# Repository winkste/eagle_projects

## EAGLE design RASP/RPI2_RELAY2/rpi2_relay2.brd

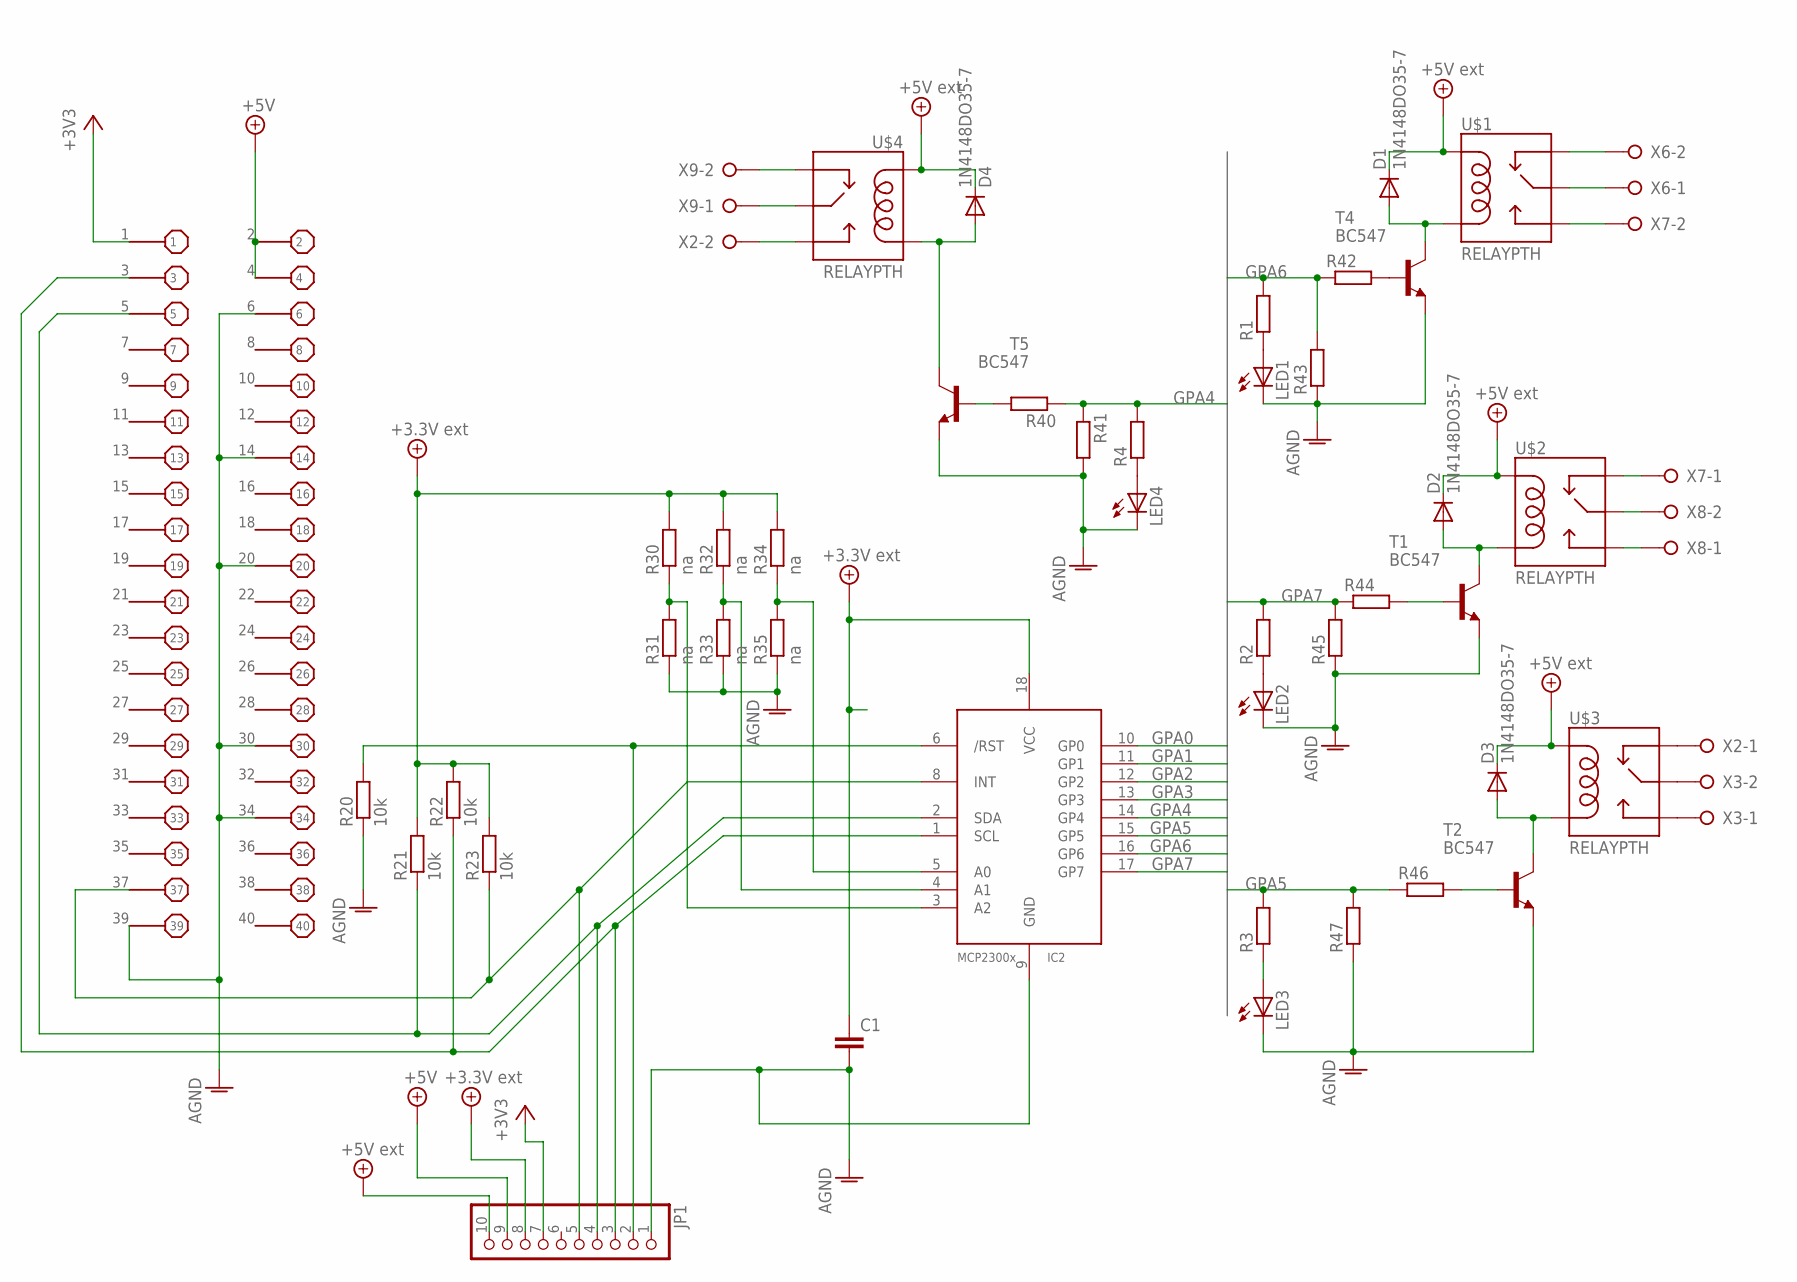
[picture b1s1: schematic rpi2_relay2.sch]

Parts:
C1: C-EUC1210; C1210
D1, D2, D3, D4: 1N4148DO35-7; DO35-7
IC2: MCP23008/P; DIL18
JP1: PINHD-1X10; 1X10
LED1, LED2, LED3, LED4: LEDCHIP-LED0805; CHIP-LED0805
R1, R2, R3, R4, R40, R41, R42, R43, R44, R45, R46, R47: R-EU_R0805; R0805
R20, R21, R22, R23: 10k; R0805
R30, R31, R32, R33, R34, R35: na; R0805
T1, T2, T4, T5: BC547; TO92
U$1, U$2, U$3, U$4: RELAYPTH; SRD-05VDC-SL-C
X1: B+_GPIO
X2, X3, X6, X7, X8, X9: W237-02P; W237-132

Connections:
3.3VEXT: C1.1, IC2.18 (VCC), JP1.8, R21.2, R22.2, R23.2, R30.2, R32.2, R34.2
+3V3: JP1.7, X1.1
+5V: JP1.9, X1.2, X1.4
+5V/1: D1.C, D2.C, D3.C, D4.C, JP1.10, U$1.COIL1, U$2.COIL1, U$3.COIL1, U$4.COIL1
AGND: C1.2, IC2.9 (GND), JP1.1, LED1.C, LED2.C, LED3.C, LED4.C, R20.1, R31.1, R33.1, R35.1, R41.2, R43.1, R45.1, R47.1, T1.1 (E), T2.1 (E), T4.1 (E), T5.1 (E), X1.6, X1.14, X1.20, X1.30, X1.34, X1.39
GPA0: IC2.10 (GP0)
GPA1: IC2.11 (GP1)
GPA2: IC2.12 (GP2)
GPA3: IC2.13 (GP3)
GPA4: IC2.14 (GP4), R4.2, R40.1, R41.1
GPA5: IC2.15 (GP5), R3.2, R46.1, R47.2
GPA6: IC2.16 (GP6), R1.2, R42.1, R43.2
GPA7: IC2.17 (GP7), R2.2, R44.1, R45.2
unnamed: R46.2, T2.2 (B)
unnamed: D1.A, T4.3 (C), U$1.COIL0
unnamed: IC2.1 (SCL), JP1.3, R22.1, X1.3
unnamed: IC2.2 (SDA), JP1.4, R21.1, X1.5
unnamed: LED1.A, R1.1
unnamed: IC2.8 (INT), JP1.5, R23.1, X1.37
unnamed: IC2.6 (/RST), JP1.2, R20.2
unnamed: R44.2, T1.2 (B)
unnamed: U$1.SWCOMMON, X6.1
unnamed: U$1.SWCLOSED (SWCLOSE), X6.2
unnamed: U$1.SWOPEN, X7.2
unnamed: D2.A, T1.3 (C), U$2.COIL0
unnamed: LED2.A, R2.1
unnamed: U$2.SWCLOSED (SWCLOSE), X7.1
unnamed: U$2.SWOPEN, X8.1
unnamed: U$2.SWCOMMON, X8.2
unnamed: D3.A, T2.3 (C), U$3.COIL0
unnamed: LED3.A, R3.1
unnamed: U$3.SWCOMMON, X3.2
unnamed: U$3.SWOPEN, X3.1
unnamed: U$3.SWCLOSED (SWCLOSE), X2.1
unnamed: D4.A, T5.3 (C), U$4.COIL0
unnamed: IC2.3 (A2), R30.1, R31.2
unnamed: U$4.SWCOMMON, X9.1
unnamed: U$4.SWOPEN, X2.2
unnamed: U$4.SWCLOSED (SWCLOSE), X9.2
unnamed: R40.2, T5.2 (B)
unnamed: R42.2, T4.2 (B)
unnamed: IC2.4 (A1), R32.1, R33.2
unnamed: IC2.5 (A0), R34.1, R35.2
unnamed: LED4.A, R4.1

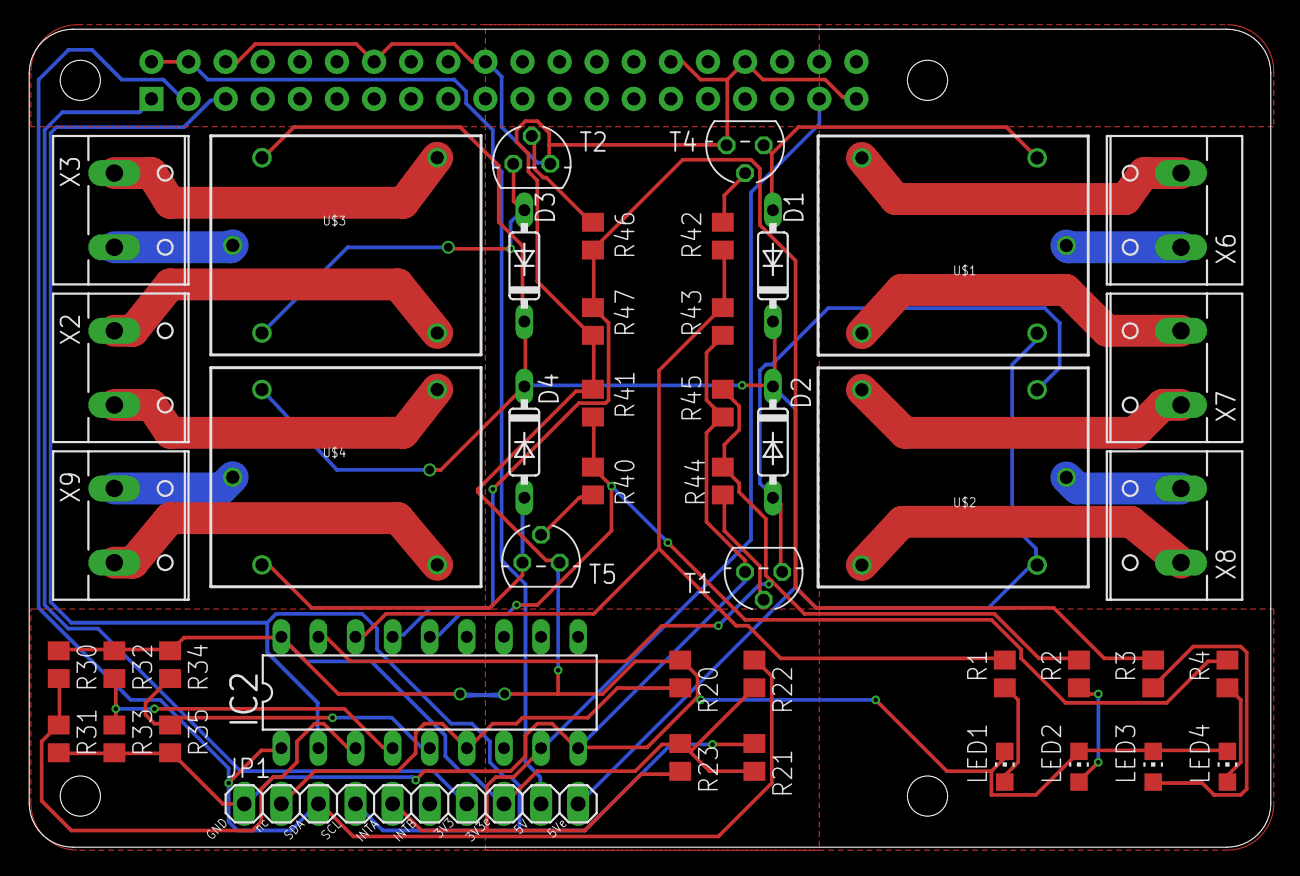
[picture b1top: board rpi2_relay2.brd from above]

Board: 2 copper layers, 85.0 x 56.0 mm, 48 parts (1 on the bottom side), 40 nets.

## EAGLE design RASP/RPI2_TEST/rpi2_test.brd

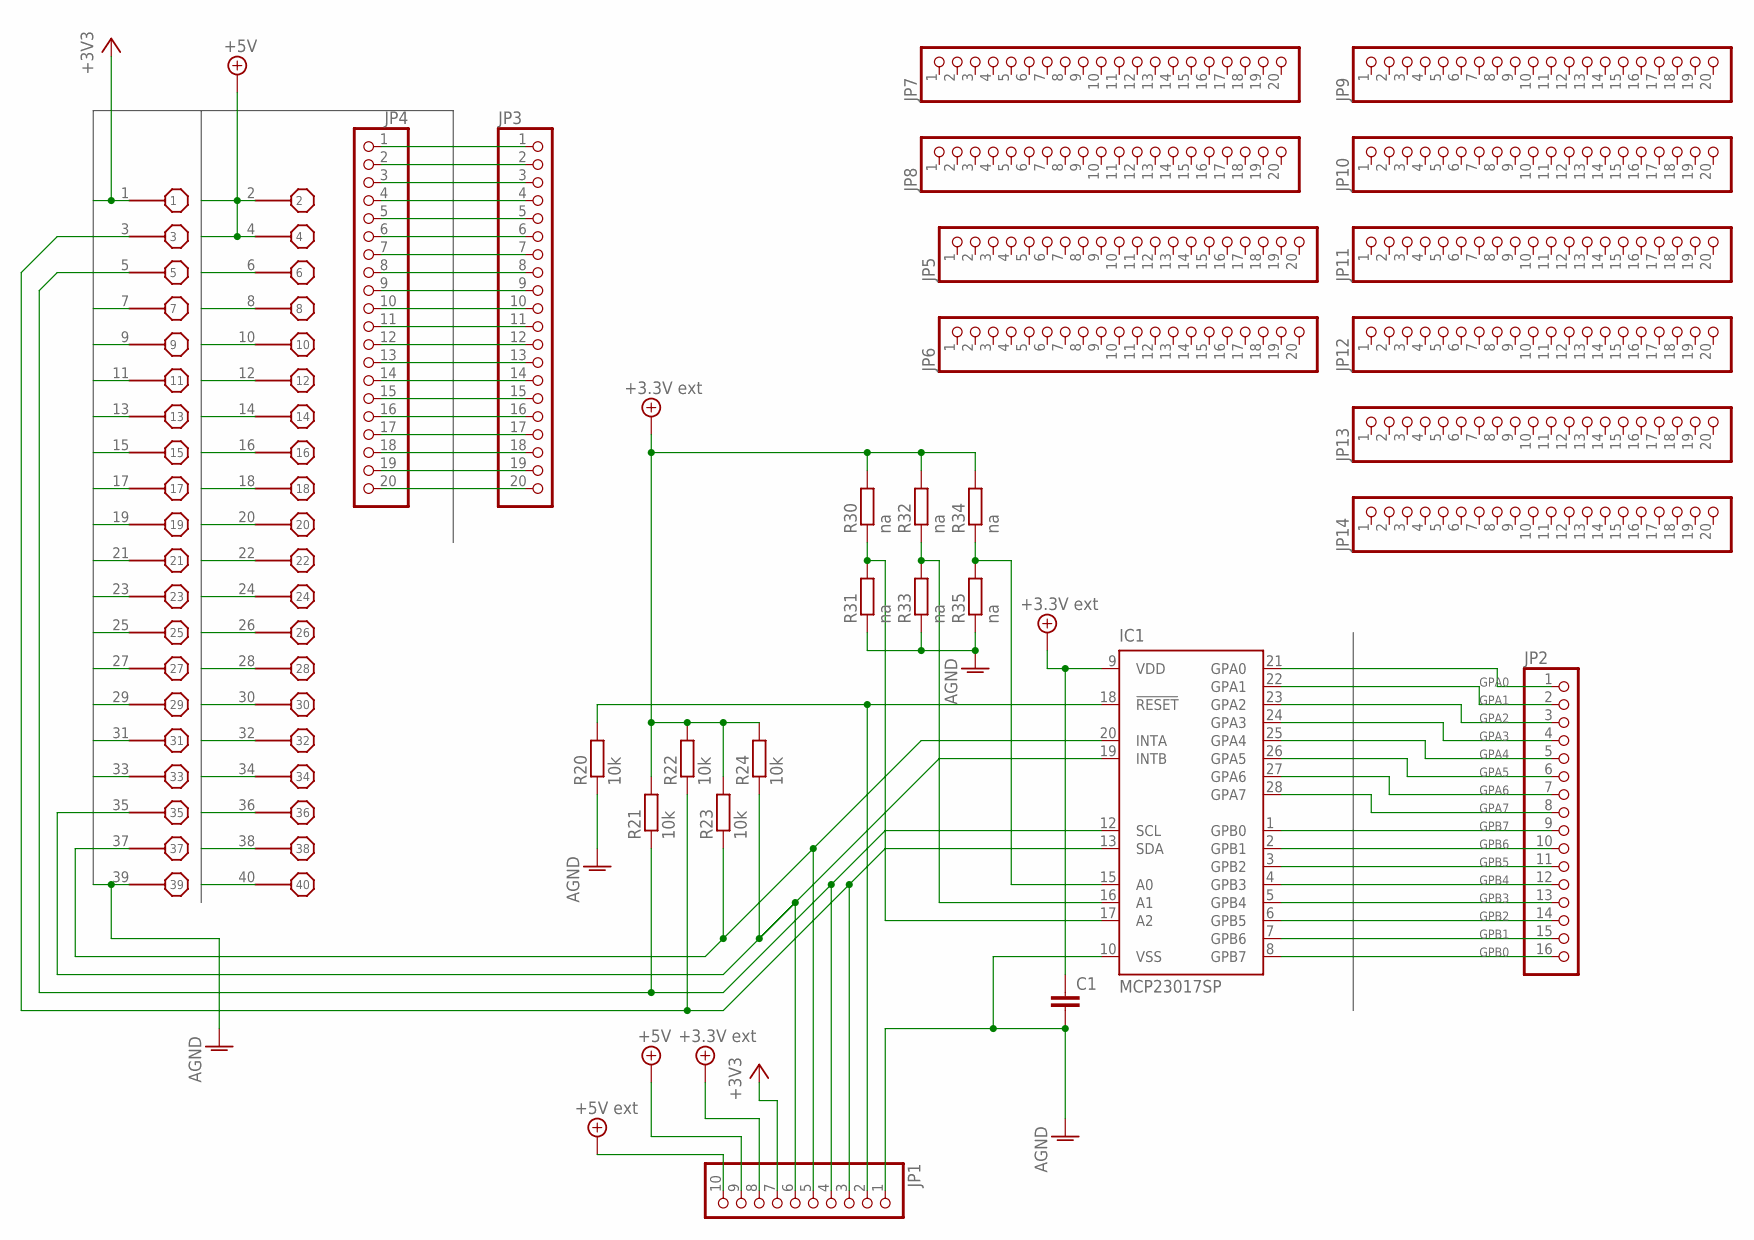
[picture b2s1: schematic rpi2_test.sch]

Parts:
C1: C-EUC1210; C1210
IC1: MCP23017SP; DIL28-3
JP1: PINHD-1X10; 1X10
JP2: PINHD-1X16; 1X16
JP3, JP4, JP5, JP6, JP7, JP8, JP9, JP10, JP11, JP12, JP13, JP14: PINHD-1X20; 1X20
R20, R21, R22, R23, R24: 10k; R0805
R30, R31, R32, R33, R34, R35: na; R0805
X1: B+_GPIO

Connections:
3.3VEXT: C1.1, IC1.9 (VDD), JP1.8, R21.2, R22.2, R23.2, R24.2, R30.2, R32.2, R34.2
+3V3: JP1.7, JP4.1, X1.1
+5V: JP1.9, JP3.1, JP3.2, X1.2, X1.4
+5V/1: JP1.10
AGND: C1.2, IC1.10 (VSS), JP1.1, R20.1, R31.1, R33.1, R35.1, X1.39
GPA0: IC1.21 (GPA0), JP2.1
GPA1: IC1.22 (GPA1), JP2.2
GPA2: IC1.23 (GPA2), JP2.3
GPA3: IC1.24 (GPA3), JP2.4
GPA4: IC1.25 (GPA4), JP2.5
GPA5: IC1.26 (GPA5), JP2.6
GPA6: IC1.27 (GPA6), JP2.7
GPA7: IC1.28 (GPA7), JP2.8
GPB0: IC1.1 (GPB0), JP2.16
GPB1: IC1.2 (GPB1), JP2.15
GPB2: IC1.3 (GPB2), JP2.14
GPB3: IC1.4 (GPB3), JP2.13
GPB4: IC1.5 (GPB4), JP2.12
GPB5: IC1.6 (GPB5), JP2.11
GPB6: IC1.7 (GPB6), JP2.10
GPB7: IC1.8 (GPB7), JP2.9
GPIO3: IC1.13 (SDA), JP1.3, JP4.2, R22.1, X1.3
GPIO5: IC1.12 (SCL), JP1.4, JP4.3, R21.1, X1.5
GPIO6: JP3.3, X1.6
GPIO7: JP4.4, X1.7
GPIO8: JP3.4, X1.8
GPIO9: JP4.5, X1.9
GPIO10: JP3.5, X1.10
GPIO11: JP4.6, X1.11
GPIO12: JP3.6, X1.12
GPIO13: JP4.7, X1.13
GPIO14: JP3.7, X1.14
GPIO15: JP4.8, X1.15
GPIO16: JP3.8, X1.16
GPIO17: JP4.9, X1.17
GPIO18: JP3.9, X1.18
GPIO19: JP4.10, X1.19
GPIO20: JP3.10, X1.20
GPIO21: JP4.11, X1.21
GPIO22: JP3.11, X1.22
GPIO23: JP4.12, X1.23
GPIO24: JP3.12, X1.24
GPIO25: JP4.13, X1.25
GPIO26: JP3.13, X1.26
GPIO27: JP4.14, X1.27
GPIO28: JP3.14, X1.28
GPIO29: JP4.15, X1.29
GPIO30: JP3.15, X1.30
GPIO31: JP4.16, X1.31
GPIO32: JP3.16, X1.32
GPIO33: JP4.17, X1.33
GPIO34: JP3.17, X1.34
GPIO35: IC1.19 (INTB), JP1.6, JP4.18, R24.1, X1.35
GPIO36: JP3.18, X1.36
GPIO37: IC1.20 (INTA), JP1.5, JP4.19, R23.1, X1.37
GPIO38: JP3.19, X1.38
GPIO39: JP4.20
GPIO40: JP3.20, X1.40
unnamed: IC1.18 (!RESET), JP1.2, R20.2
unnamed: IC1.17 (A2), R30.1, R31.2
unnamed: IC1.16 (A1), R32.1, R33.2
unnamed: IC1.15 (A0), R34.1, R35.2

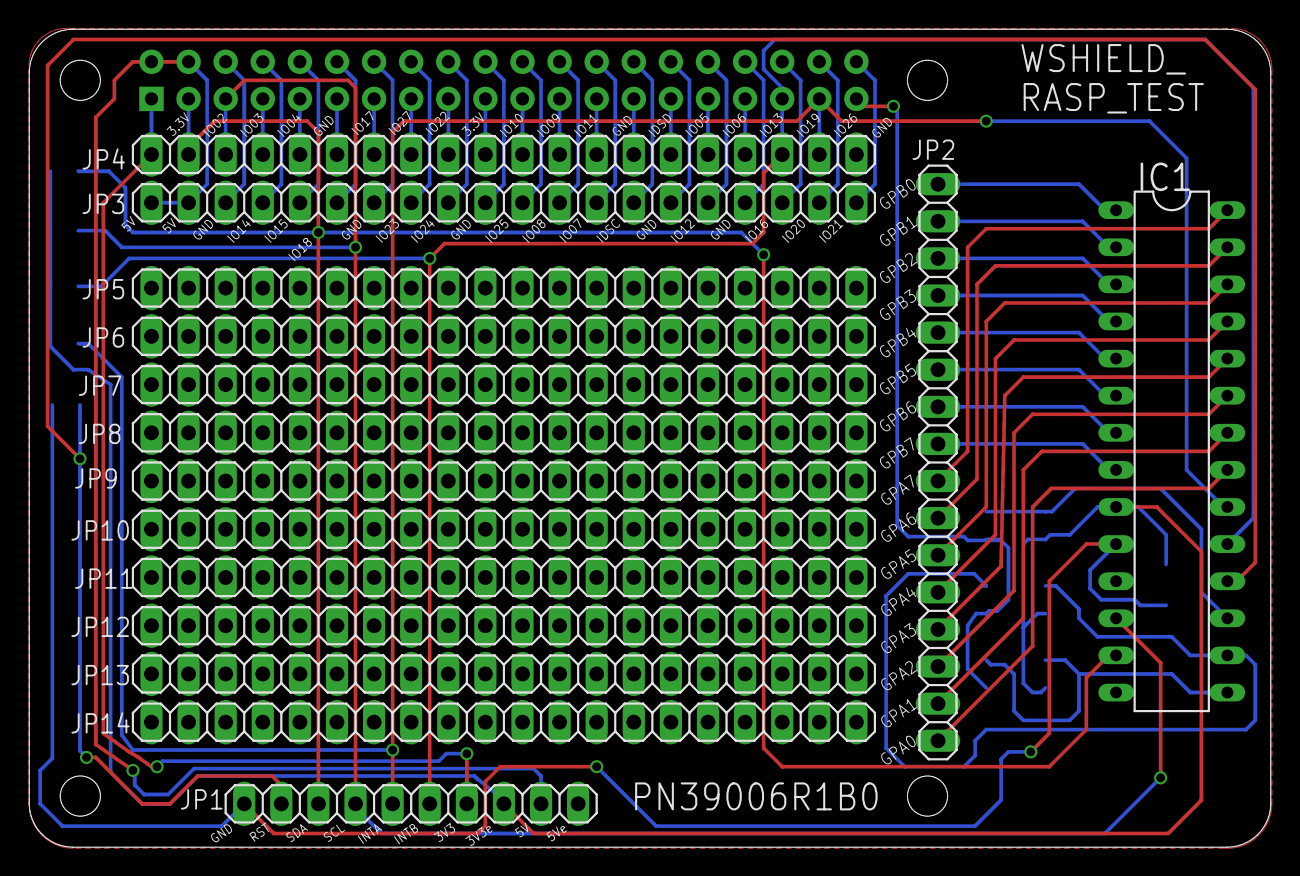
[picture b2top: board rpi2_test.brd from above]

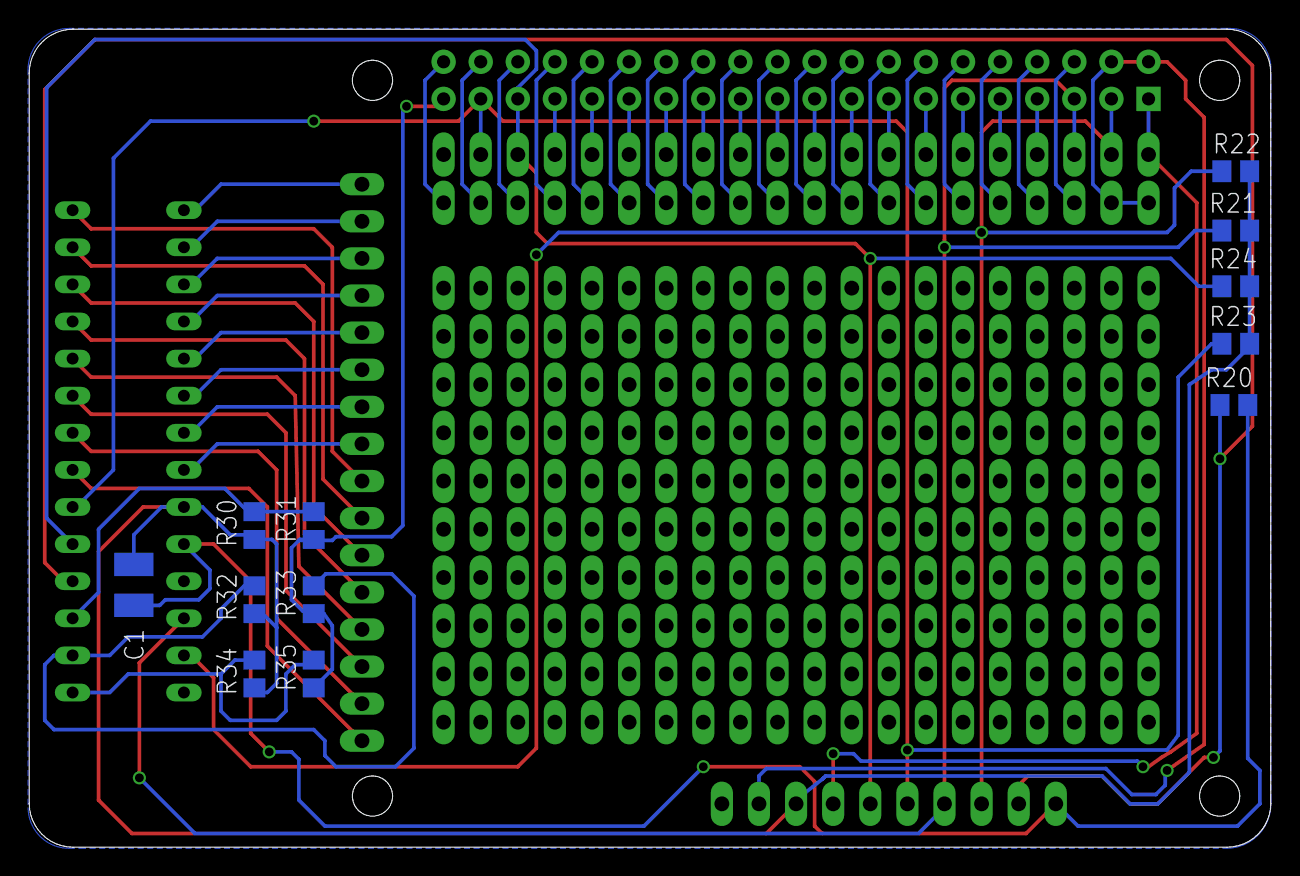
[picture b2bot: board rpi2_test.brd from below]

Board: 2 copper layers, 85.0 x 56.0 mm, 28 parts (12 on the bottom side), 60 nets.

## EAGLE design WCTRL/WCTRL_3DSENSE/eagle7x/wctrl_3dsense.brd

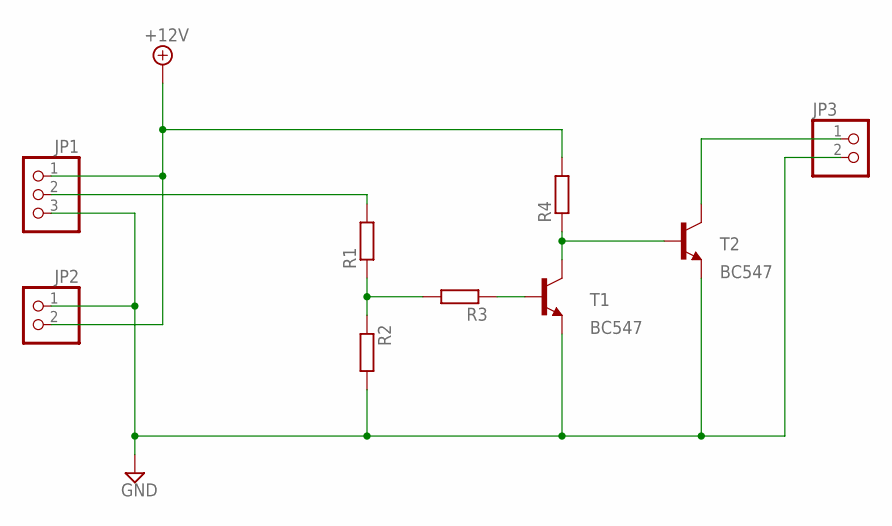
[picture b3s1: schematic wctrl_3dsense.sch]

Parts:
JP1: PINHD-1X3; 1X03
JP2, JP3: PINHD-1X2; 1X02
R1, R2, R3, R4: R-EU_0207/10; 0207/10
T1, T2: BC547; TO92

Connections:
+12V: JP1.1, JP2.2, R4.2
GND: JP1.3, JP2.1, JP3.2, R2.2, T1.1 (E), T2.1 (E)
unnamed: JP1.2, R1.2
unnamed: R1.1, R2.1, R3.2
unnamed: R3.1, T1.2 (B)
unnamed: JP3.1, T2.3 (C)
unnamed: R4.1, T1.3 (C), T2.2 (B)

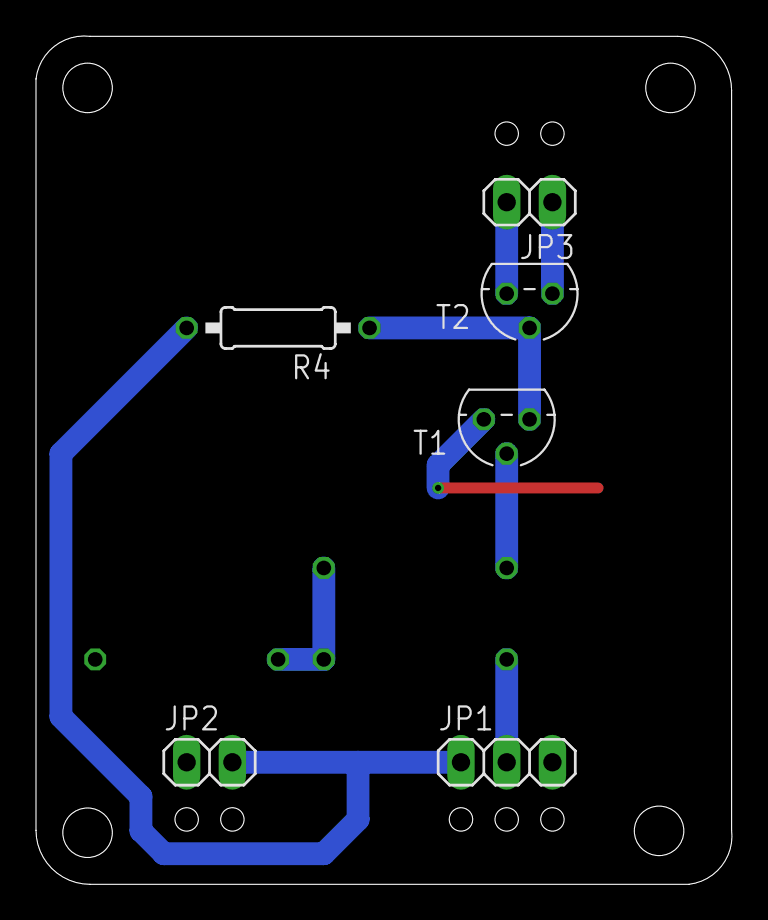
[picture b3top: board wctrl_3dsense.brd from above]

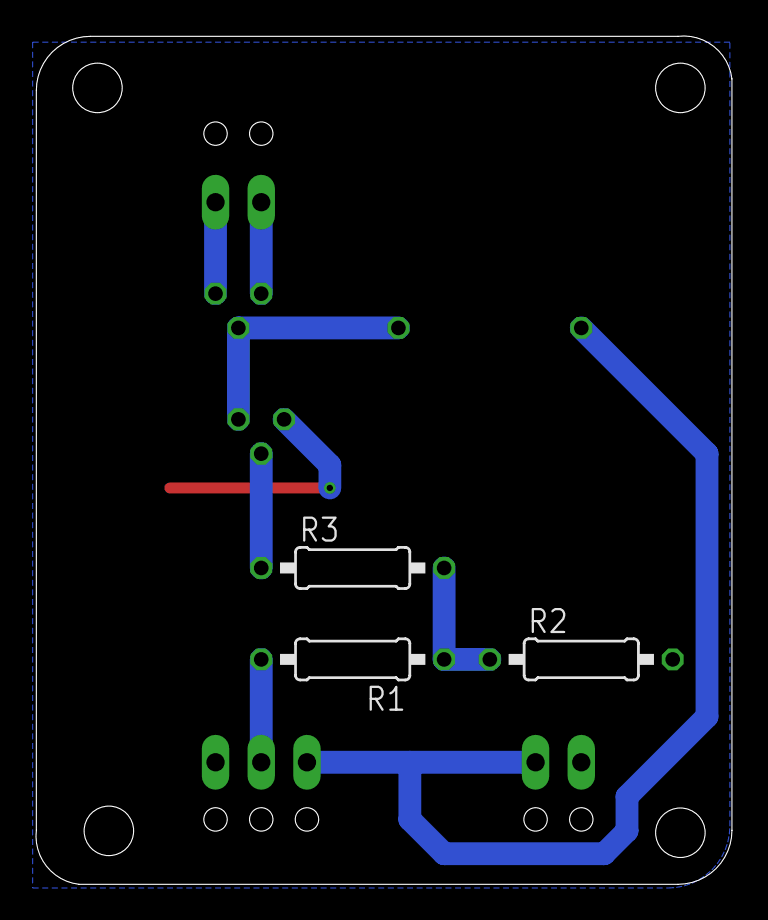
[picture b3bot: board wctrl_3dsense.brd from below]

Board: 2 copper layers, 38.7 x 47.1 mm, 9 parts (3 on the bottom side), 7 nets.

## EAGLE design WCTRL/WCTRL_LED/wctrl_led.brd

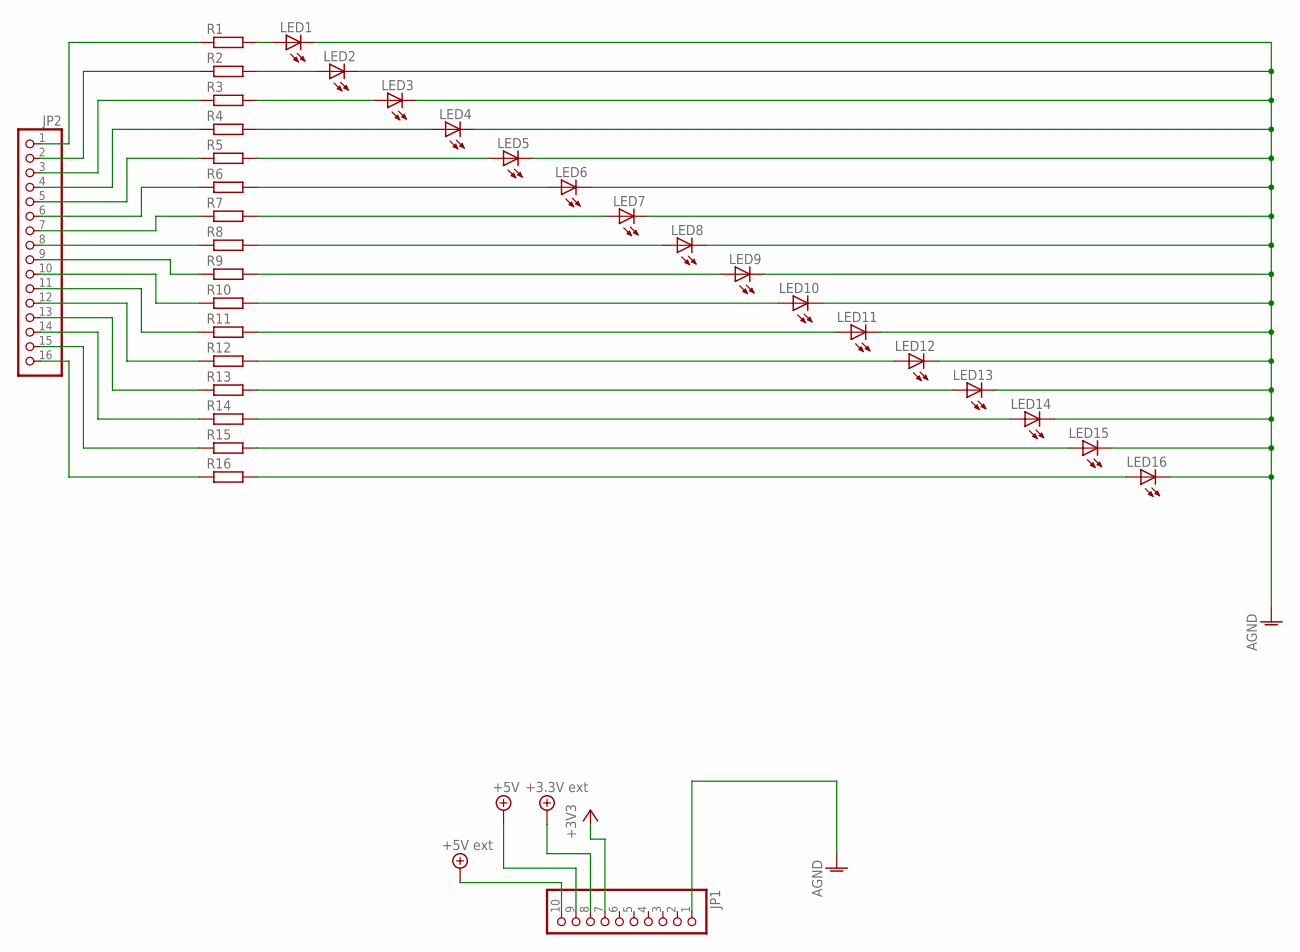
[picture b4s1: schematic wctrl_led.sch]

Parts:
JP1: PINHD-1X10; 1X10
JP2: PINHD-1X16; 1X16
LED1, LED2, LED3, LED4, LED5, LED6, LED7, LED8, LED9, LED10, LED11, LED12, LED13, LED14, LED15, LED16: LED5MM
R1, R2, R3, R4, R5, R6, R7, R8, R9, R10, R11, R12, R13, R14, R15, R16: R-EU_0207/10; 0207/10

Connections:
3.3VEXT: JP1.8
+3V3: JP1.7
+5V: JP1.9
+5V/1: JP1.10
AGND: JP1.1, LED1.K (C), LED2.K (C), LED3.K (C), LED4.K (C), LED5.K (C), LED6.K (C), LED7.K (C), LED8.K (C), LED9.K (C), LED10.K (C), LED11.K (C), LED12.K (C), LED13.K (C), LED14.K (C), LED15.K (C), LED16.K (C)
unnamed: JP2.1, R1.1
unnamed: LED1.A, R1.2
unnamed: JP2.2, R2.1
unnamed: JP2.3, R3.1
unnamed: JP2.4, R4.1
unnamed: JP2.5, R5.1
unnamed: JP2.6, R6.1
unnamed: JP2.7, R7.1
unnamed: JP2.8, R8.1
unnamed: JP2.16, R16.1
unnamed: JP2.15, R15.1
unnamed: JP2.14, R14.1
unnamed: JP2.13, R13.1
unnamed: JP2.12, R12.1
unnamed: JP2.11, R11.1
unnamed: JP2.10, R10.1
unnamed: JP2.9, R9.1
unnamed: LED2.A, R2.2
unnamed: LED3.A, R3.2
unnamed: LED4.A, R4.2
unnamed: LED5.A, R5.2
unnamed: LED6.A, R6.2
unnamed: LED7.A, R7.2
unnamed: LED8.A, R8.2
unnamed: LED9.A, R9.2
unnamed: LED10.A, R10.2
unnamed: LED11.A, R11.2
unnamed: LED12.A, R12.2
unnamed: LED13.A, R13.2
unnamed: LED14.A, R14.2
unnamed: LED15.A, R15.2
unnamed: LED16.A, R16.2

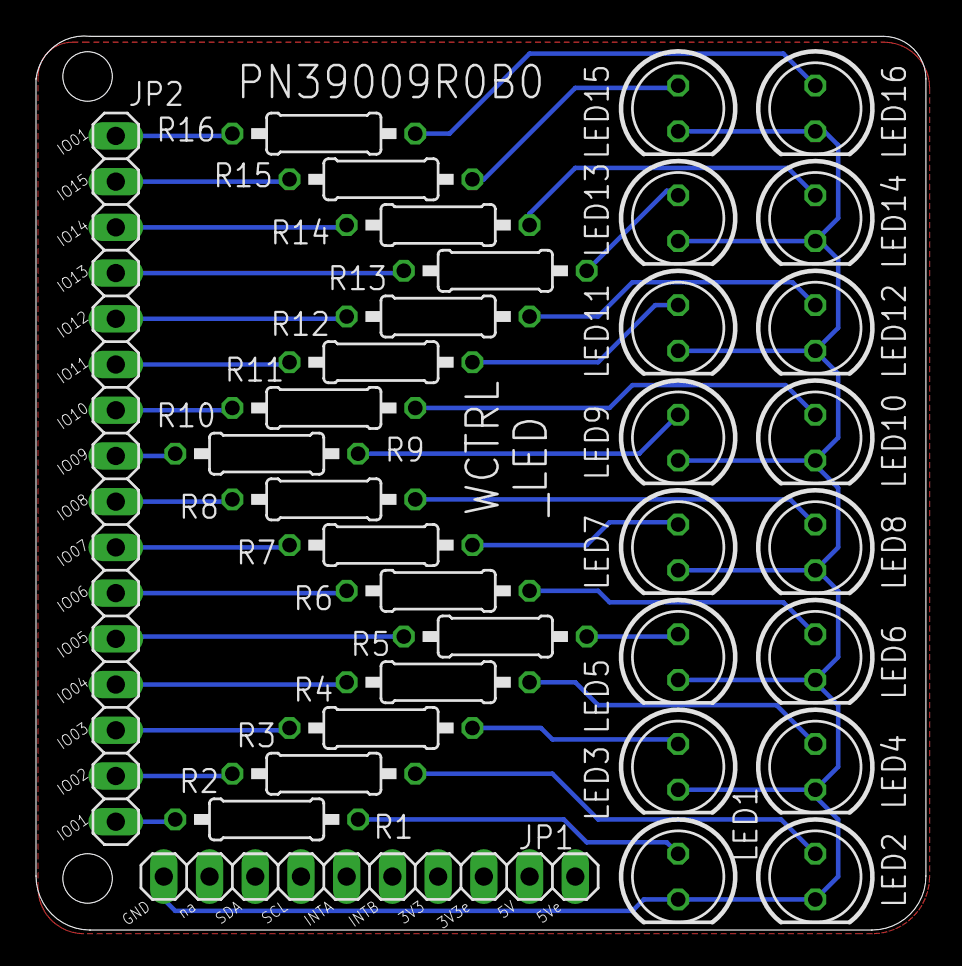
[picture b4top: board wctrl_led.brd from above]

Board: 2 copper layers, 49.4 x 49.7 mm, 34 parts (0 on the bottom side), 33 nets.

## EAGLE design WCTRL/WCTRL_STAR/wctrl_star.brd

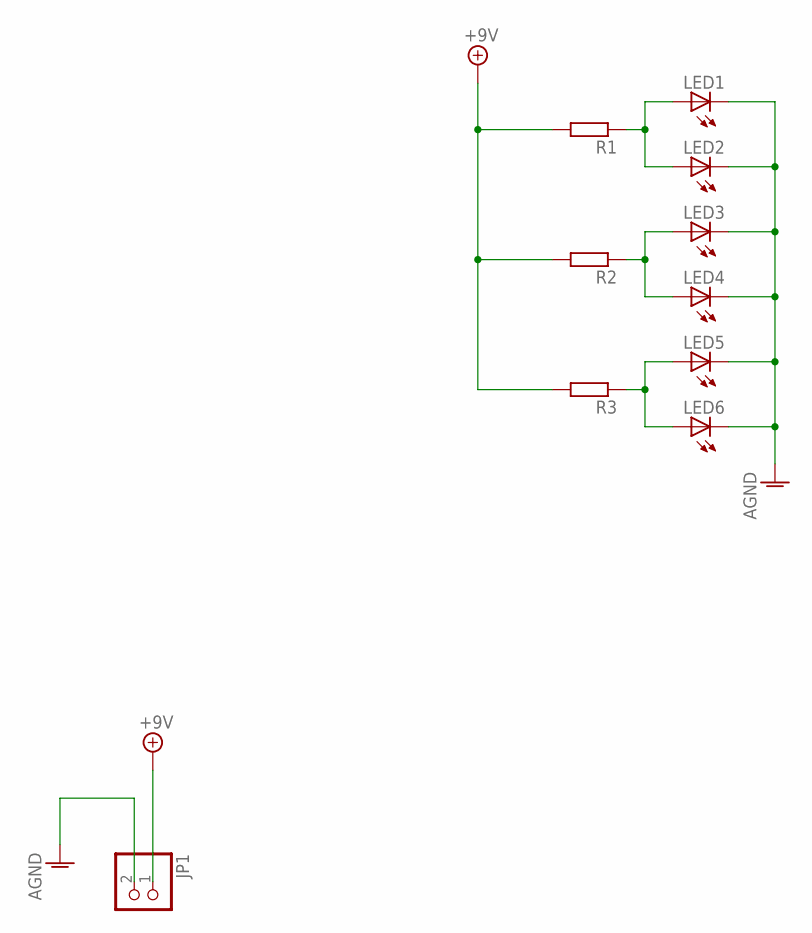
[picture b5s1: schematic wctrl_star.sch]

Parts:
JP1: PINHD-1X2; 1X02
LED1, LED2, LED3, LED4, LED5, LED6: LED3MM
R1, R2, R3: R-EU_0207/10; 0207/10

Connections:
+9V: JP1.1, R1.2, R2.2, R3.2
AGND: JP1.2, LED1.K (C), LED2.K (C), LED3.K (C), LED4.K (C), LED5.K (C), LED6.K (C)
unnamed: LED1.A, LED2.A, R1.1
unnamed: LED3.A, LED4.A, R2.1
unnamed: LED5.A, LED6.A, R3.1

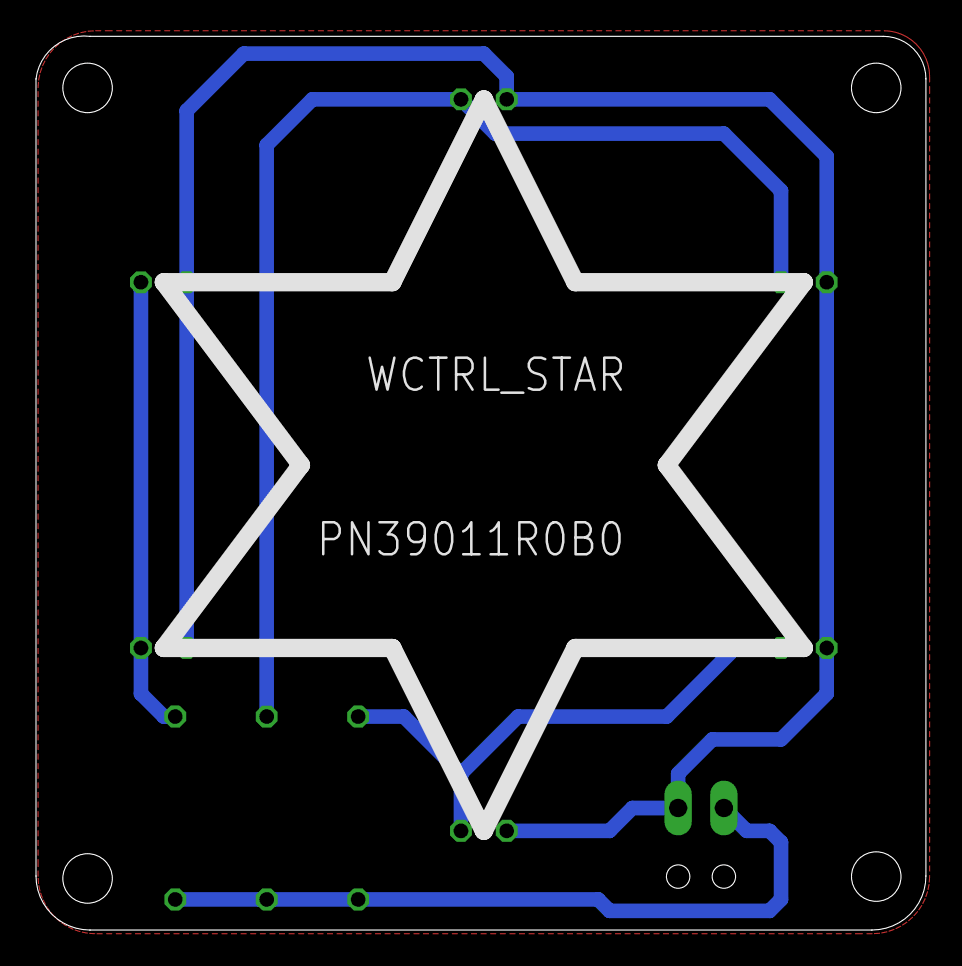
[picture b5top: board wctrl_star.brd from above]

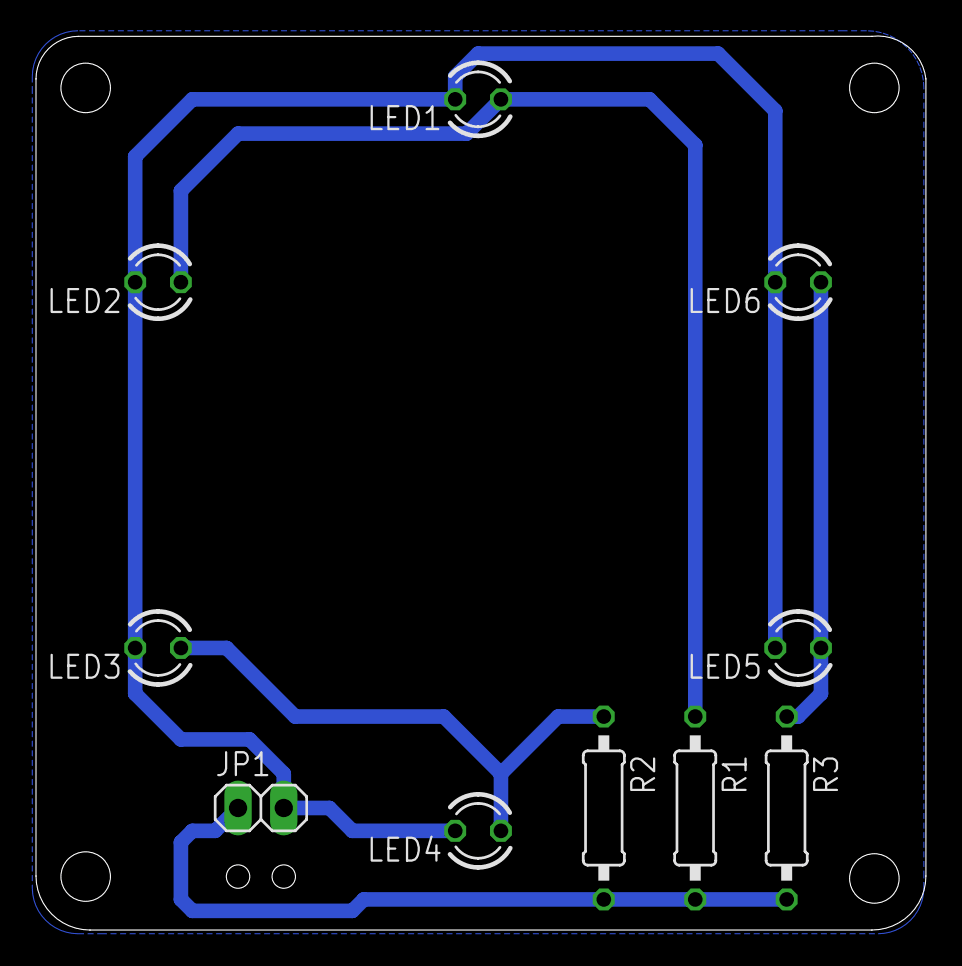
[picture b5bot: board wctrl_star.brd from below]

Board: 2 copper layers, 49.4 x 49.7 mm, 10 parts (10 on the bottom side), 5 nets.

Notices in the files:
parts and their libraries:
diy-modules: Released under the Creative Commons Attribution 4.0 International License: http://creativecommons.org/licenses/by/4.0
